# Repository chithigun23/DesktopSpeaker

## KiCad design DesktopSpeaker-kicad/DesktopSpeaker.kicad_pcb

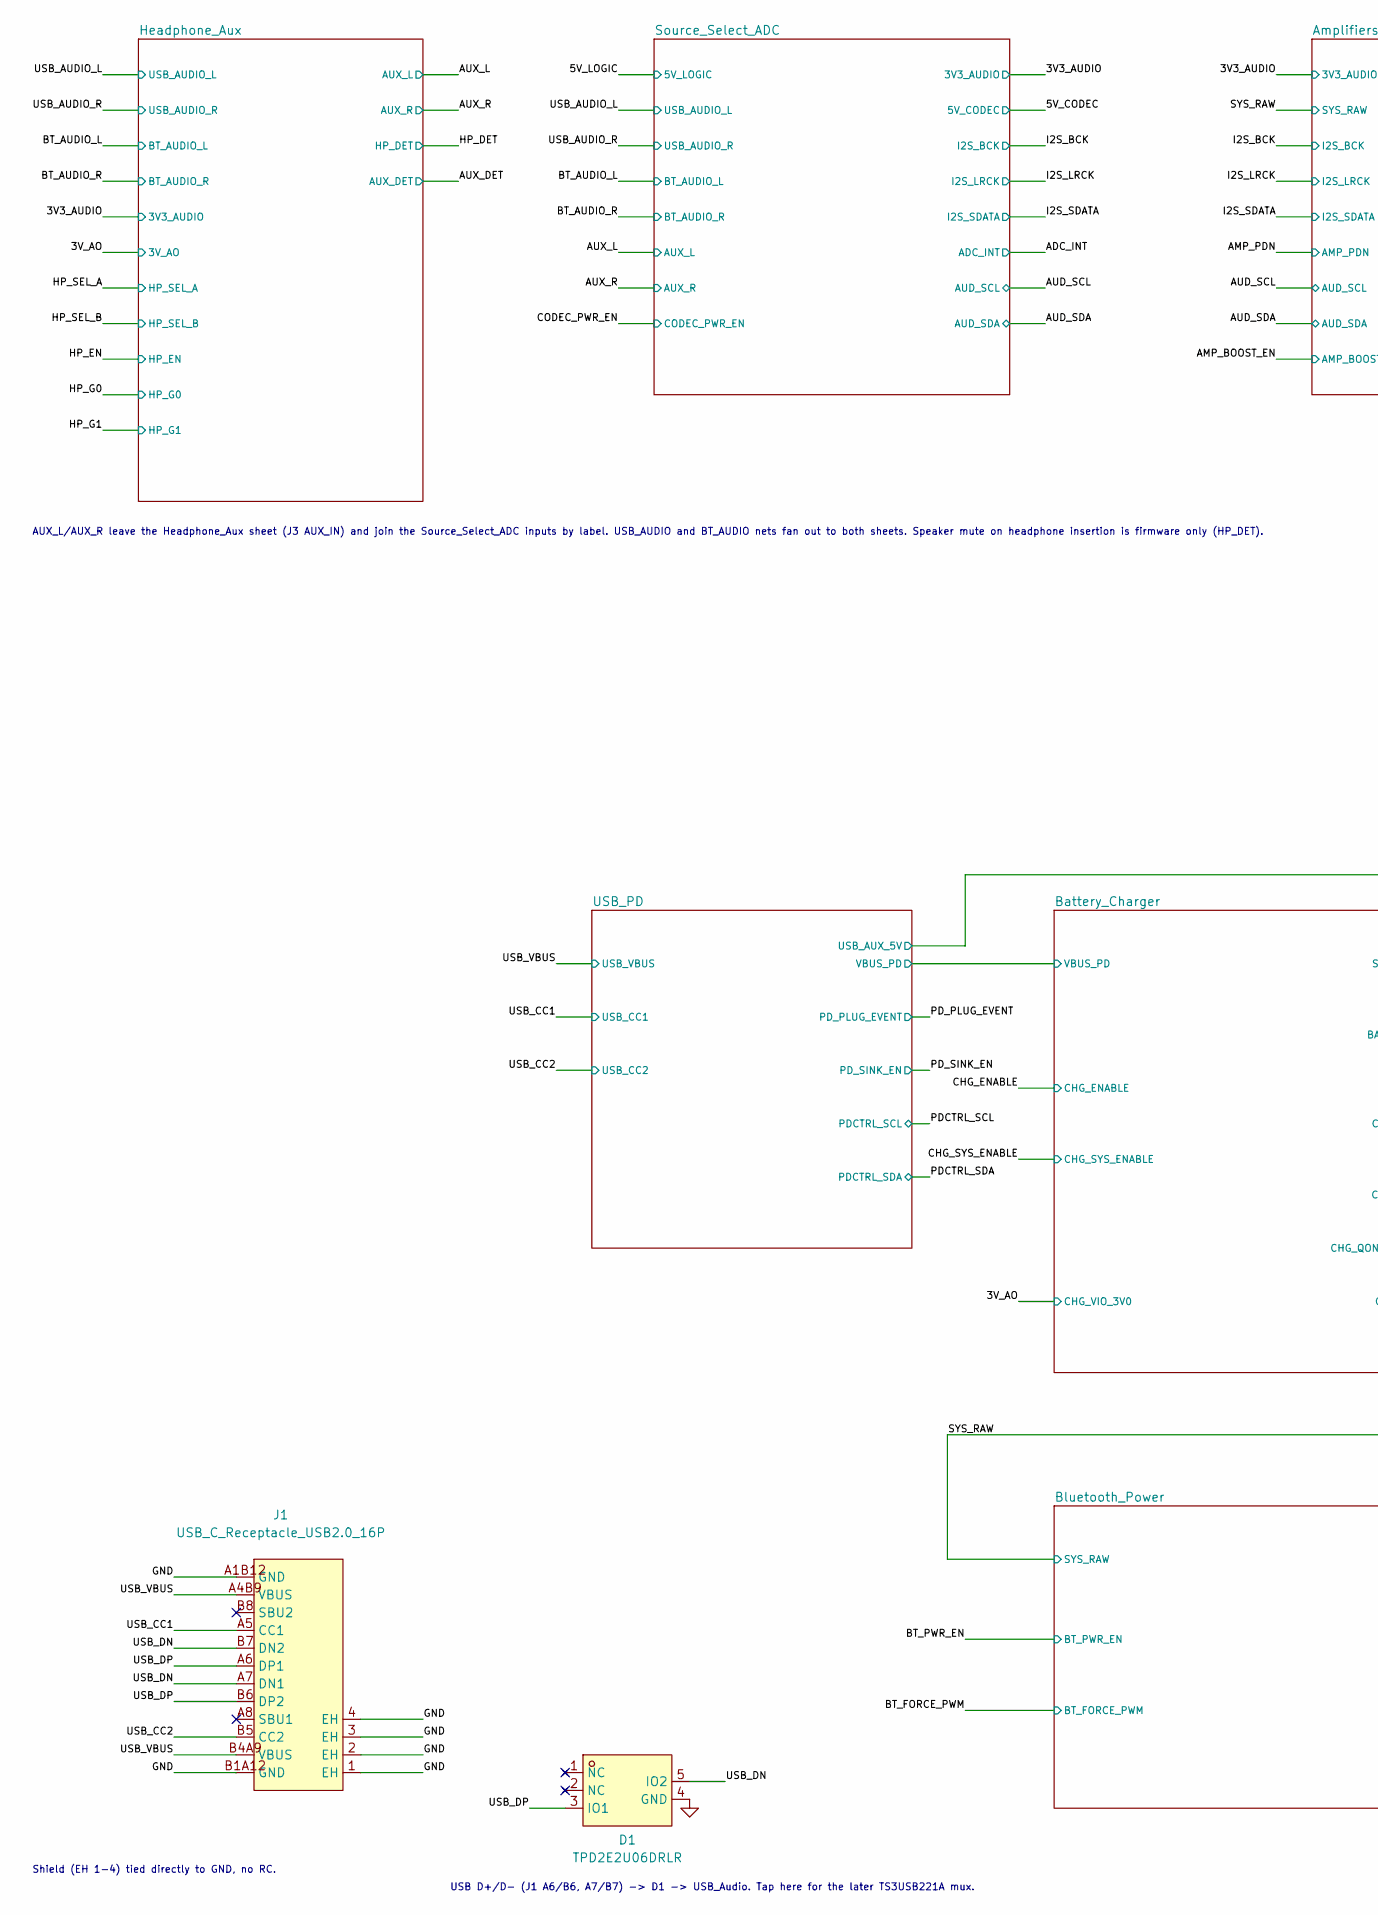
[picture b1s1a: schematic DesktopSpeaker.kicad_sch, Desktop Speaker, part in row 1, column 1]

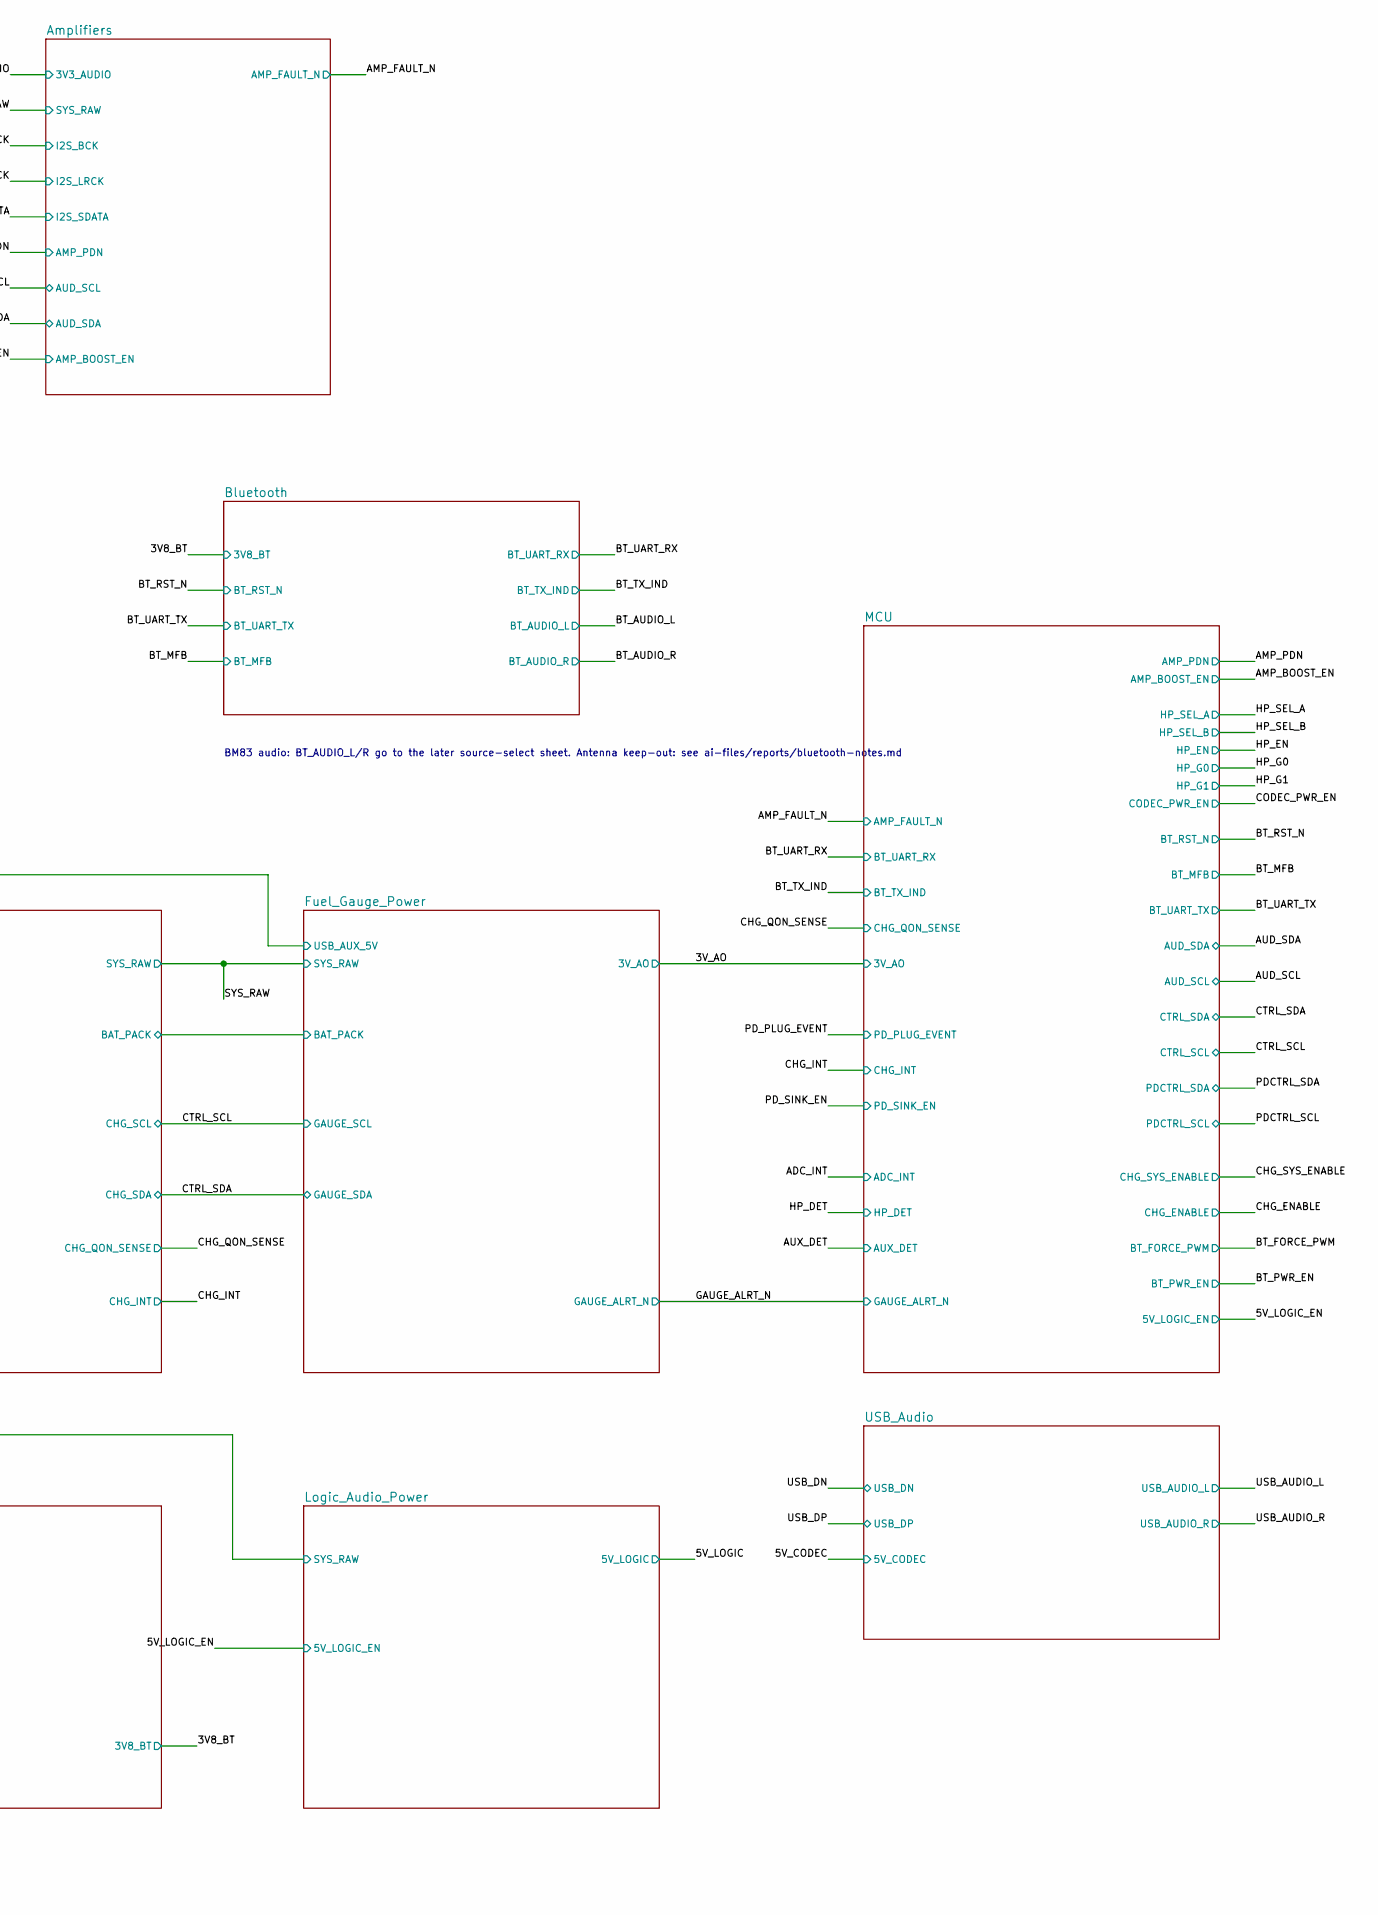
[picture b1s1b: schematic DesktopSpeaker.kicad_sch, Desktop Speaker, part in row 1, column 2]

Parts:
D1: TPD2E2U06DRLR; MPN TPD2E2U06DRLR; LCSC Part C1972959
J1: USB_C_Receptacle_USB2.0_16P; TYPE-C-31-M-12; MPN TYPE-C-31-M-12; LCSC Part C165948

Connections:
/USB_CC1: J1.A5 (CC1); also elsewhere on the board
/USB_CC2: J1.B5 (CC2); also elsewhere on the board
/USB_DN: D1.5 (IO2), J1.A7 (DN1), J1.B7 (DN2); also elsewhere on the board
/USB_DP: D1.3 (IO1), J1.A6 (DP1), J1.B6 (DP2); also elsewhere on the board
/USB_VBUS: J1.A4B9 (VBUS), J1.B4A9 (VBUS); also elsewhere on the board
GND: D1.4 (GND), J1.1 (EH), J1.2 (EH), J1.3 (EH), J1.4 (EH), J1.A1B12 (GND), J1.B1A12 (GND); also elsewhere on the board

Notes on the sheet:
USB D+/D- (J1 A6/B6, A7/B7) -> D1 -> USB_Audio. Tap here for the later TS3USB221A mux.
Shield (EH 1-4) tied directly to GND, no RC.
BM83 audio: BT_AUDIO_L/R go to the later source-select sheet. Antenna keep-out: see ai-files/reports/bluetooth-notes.md
AUX_L/AUX_R leave the Headphone_Aux sheet (J3 AUX_IN) and join the Source_Select_ADC inputs by label. USB_AUDIO and BT_AUDIO nets fan out to both sheets. Speaker mute on headphone insertion is firmware only (HP_DET).

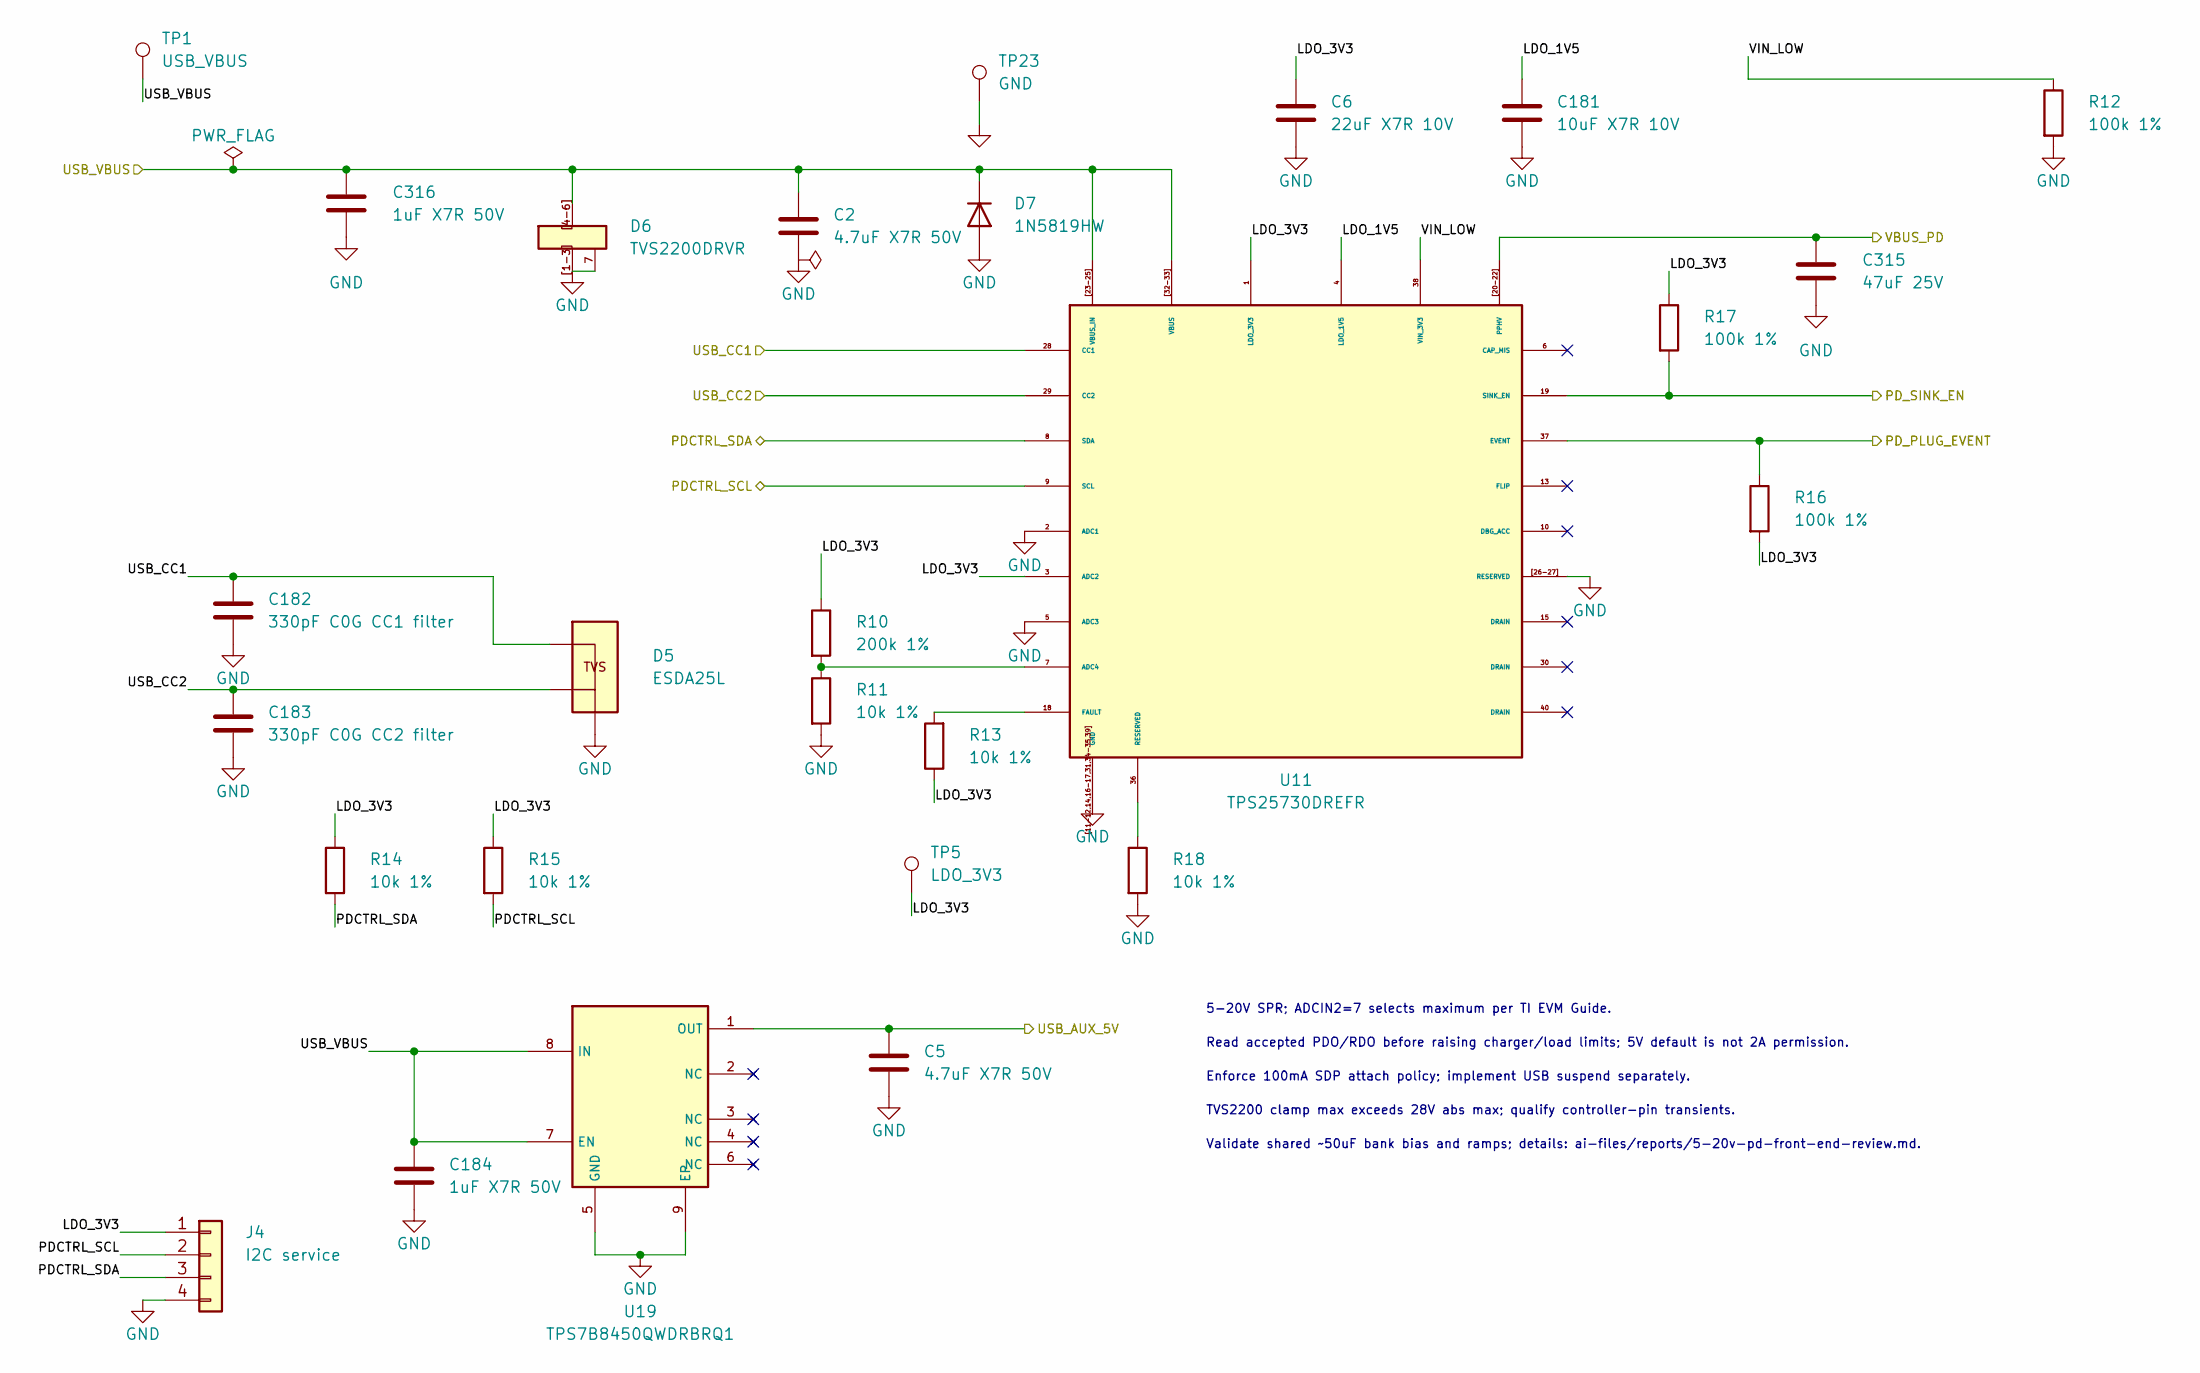
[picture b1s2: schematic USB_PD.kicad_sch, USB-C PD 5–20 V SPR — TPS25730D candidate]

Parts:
C2: 4.7uF X7R 50V; C_0805_2012Metric_Pad1.18x1.45mm_HandSolder; MPN C2012X7R1H475KT0A0E; LCSC Part C5159426
C5: 4.7uF X7R 50V; C_0805_2012Metric_Pad1.18x1.45mm_HandSolder; MPN C2012X7R1H475KT0A0E; LCSC C5159426
C6: 22uF X7R 10V; C_0805_2012Metric_Pad1.18x1.45mm_HandSolder; MPN GRM21BZ71A226ME15L; LCSC Part C907991
C181: 10uF X7R 10V; C_0805_2012Metric_Pad1.18x1.45mm_HandSolder; MPN CL21B106KPQNNNE; LCSC Part C32635
C182: 330pF C0G CC1 filter; C_0402_1005Metric_Pad0.74x0.62mm_HandSolder; MPN GRM1555C1H331JA01D; LCSC C76965
C183: 330pF C0G CC2 filter; C_0402_1005Metric_Pad0.74x0.62mm_HandSolder; MPN GRM1555C1H331JA01D; LCSC C76965
C184: 1uF X7R 50V; C_0805_2012Metric_Pad1.18x1.45mm_HandSolder; MPN CL21B105KBFNNNE; LCSC Part C28323
C315: 47uF 25V; PD_C_1206; MPN GRM31CR61E476ME44L; LCSC C403725
C316: 1uF X7R 50V; C_0805_2012Metric_Pad1.18x1.45mm_HandSolder; MPN CL21B105KBFNNNE; LCSC C28323
D5: ESDA25L; MPN ESDA25L; LCSC Part C95343
D6: TVS2200DRVR; MPN TVS2200DRVR; LCSC C523793
D7: 1N5819HW; PD_D_SOD123; MPN 1N5819HW-7-F; LCSC Part C82544
J4: I2C service; PD_SERVICE_HDR; MPN B-2100S04P-A110; LCSC C124378
R10: 200k 1%; R_0402_1005Metric_Pad0.72x0.64mm_HandSolder; MPN RC0402FR-07200KL; LCSC C114763
R11, R13, R14, R15, R18: 10k 1%; R_0402_1005Metric_Pad0.72x0.64mm_HandSolder; MPN RC0402FR-0710KL; LCSC Part C60490
R12, R16, R17: 100k 1%; R_0402_1005Metric_Pad0.72x0.64mm_HandSolder; MPN RC0402FR-07100KL; LCSC Part C60491
TP1: USB_VBUS; TestPoint_Keystone_5015_Micro_Mini
TP5: LDO_3V3; TestPoint_Keystone_5015_Micro_Mini
TP23: GND; TestPoint_Keystone_5010-5014_Multipurpose
U11: TPS25730DREFR; TPS25730D; MPN TPS25730DREFR; LCSC Part C22438973
U19: TPS7B8450QWDRBRQ1; TPS7B8450QWDRBRQ1_WSON-8; MPN TPS7B8450QWDRBRQ1; LCSC Part C3751394

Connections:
/Battery_Charger/VBUS_PD: C315.1, U11.20, U11.[20-22] (PPHV); also elsewhere on the board
/Fuel_Gauge_Power/USB_AUX_5V: C5.1, U19.1 (OUT); also elsewhere on the board
/PDCTRL_SCL: J4.2, R15.2, U11.9 (SCL); also elsewhere on the board
/PDCTRL_SDA: J4.3, R14.2, U11.8 (SDA); also elsewhere on the board
/PD_PLUG_EVENT: R16.1, U11.37 (EVENT); also elsewhere on the board
/PD_SINK_EN: R17.2, U11.19 (SINK_EN); also elsewhere on the board
/USB_CC1: C182.1, D5.1 (CC1/K1), U11.28 (CC1); also elsewhere on the board
/USB_CC2: C183.1, D5.2 (CC2/K2), U11.29 (CC2); also elsewhere on the board
/USB_PD/LDO_1V5: C181.1, U11.4 (LDO_1V5)
/USB_PD/LDO_3V3: C6.1, J4.1, R10.1, R13.1, R14.1, R15.1, R16.2, R17.1, TP5.1, U11.1 (LDO_3V3), U11.3 (ADC2)
/USB_PD/VIN_LOW: R12.1, U11.38 (VIN_3V3)
/USB_VBUS: C2.1, C184.1, C316.1, D6.4, D6.5, D6.6, D6.[4-6] (IN), D7.1 (K), TP1.1, U11.23, U11.32, U11.[23-25] (VBUS_IN), U11.[32-33] (VBUS), U19.7 (EN), U19.8 (IN); also elsewhere on the board
GND: C2.2, C5.2, C6.2, C181.2, C182.2, C183.2, C184.2, C315.2, C316.2, D5.3 (GND/A), D6.1, D6.2, D6.3, D6.7 (EP), D6.[1-3] (GND), D7.2 (A), J4.4, R11.2, R12.2, R18.2, TP23.1, U11.2 (ADC1), U11.5 (ADC3), U11.11, U11.12, U11.14, U11.16, U11.17, U11.26, U11.27, U11.31, U11.34, U11.39, U11.[11-12,14,16-17,31,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 (GND), U11.[26-27] (RESERVED), U19.5 (GND), U19.9 (EP); also elsewhere on the board
unnamed: R18.1, U11.36 (RESERVED)
unnamed: R10.2, R11.1, U11.7 (ADC4)
unnamed: R13.2, U11.18 (FAULT)

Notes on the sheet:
5-20V SPR; ADCIN2=7 selects maximum per TI EVM Guide.
Read accepted PDO/RDO before raising charger/load limits; 5V default is not 2A permission.
Enforce 100mA SDP attach policy; implement USB suspend separately.
TVS2200 clamp max exceeds 28V abs max; qualify controller-pin transients.
Validate shared ~50uF bank bias and ramps; details: ai-files/reports/5-20v-pd-front-end-review.md.

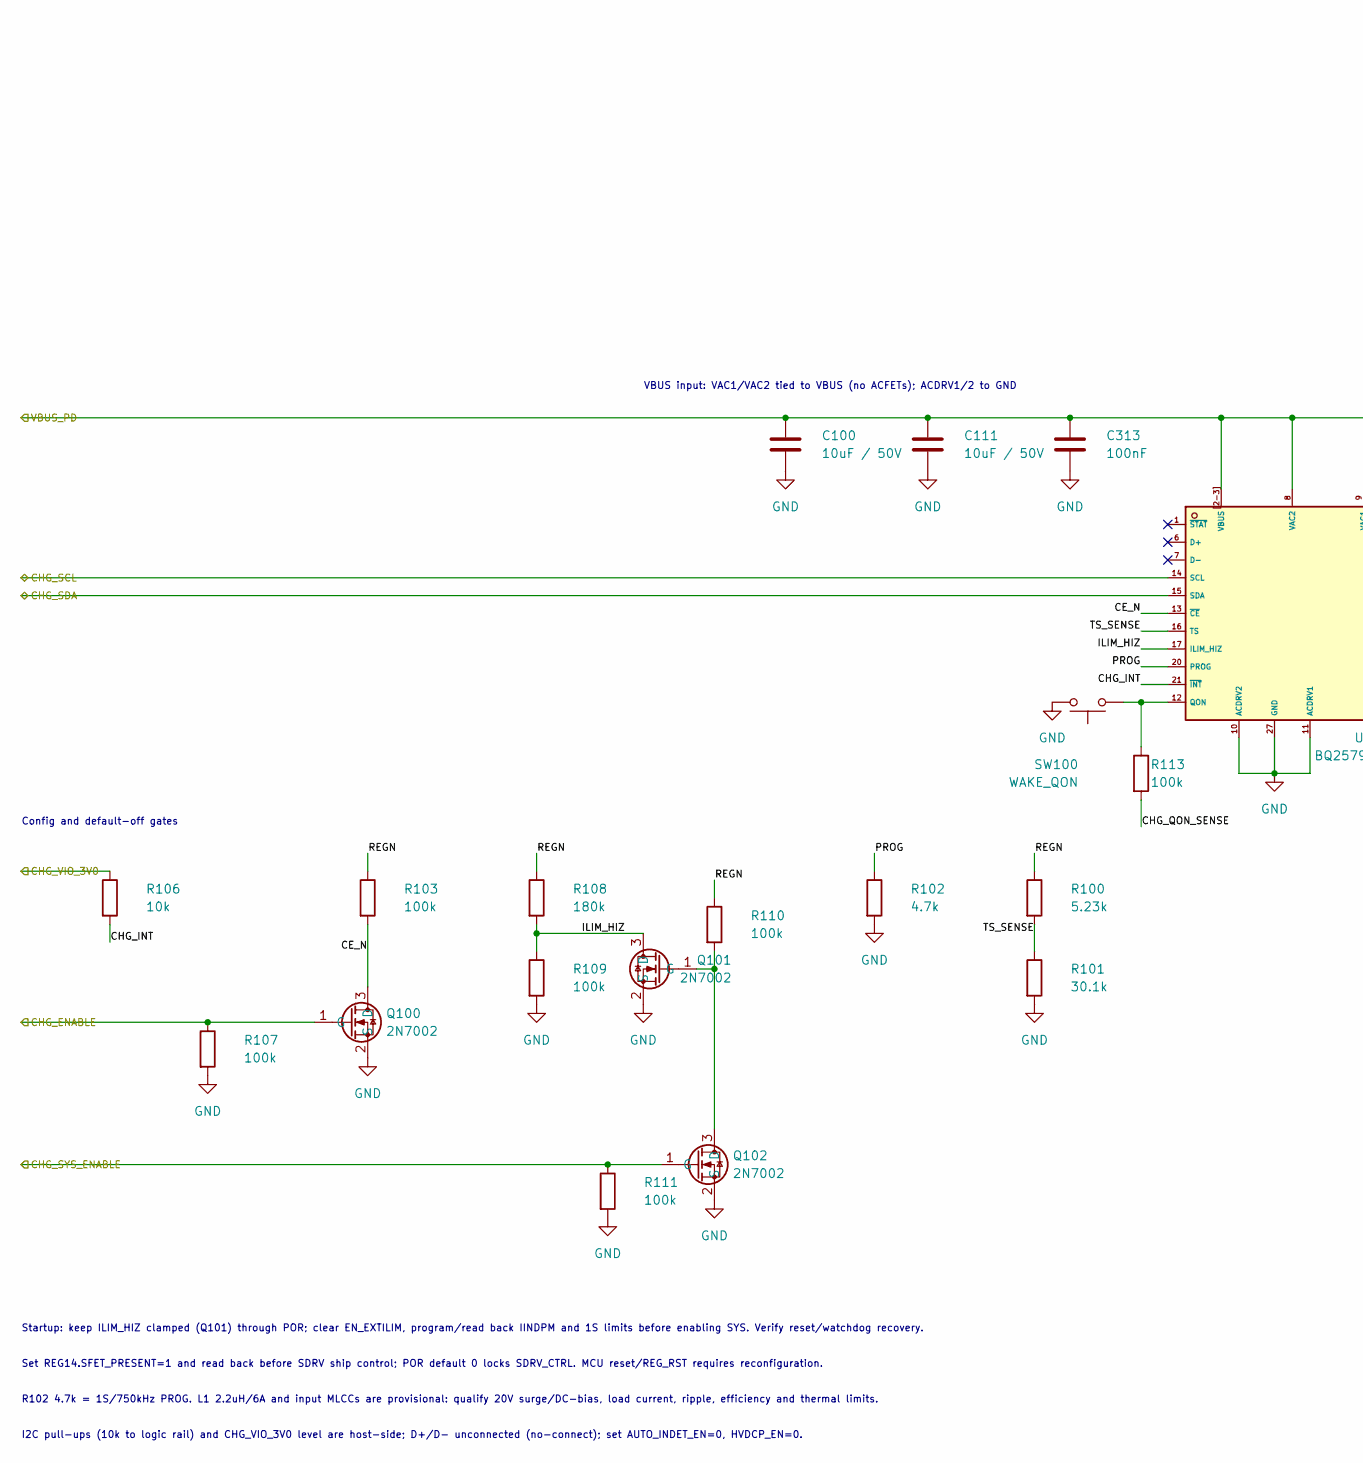
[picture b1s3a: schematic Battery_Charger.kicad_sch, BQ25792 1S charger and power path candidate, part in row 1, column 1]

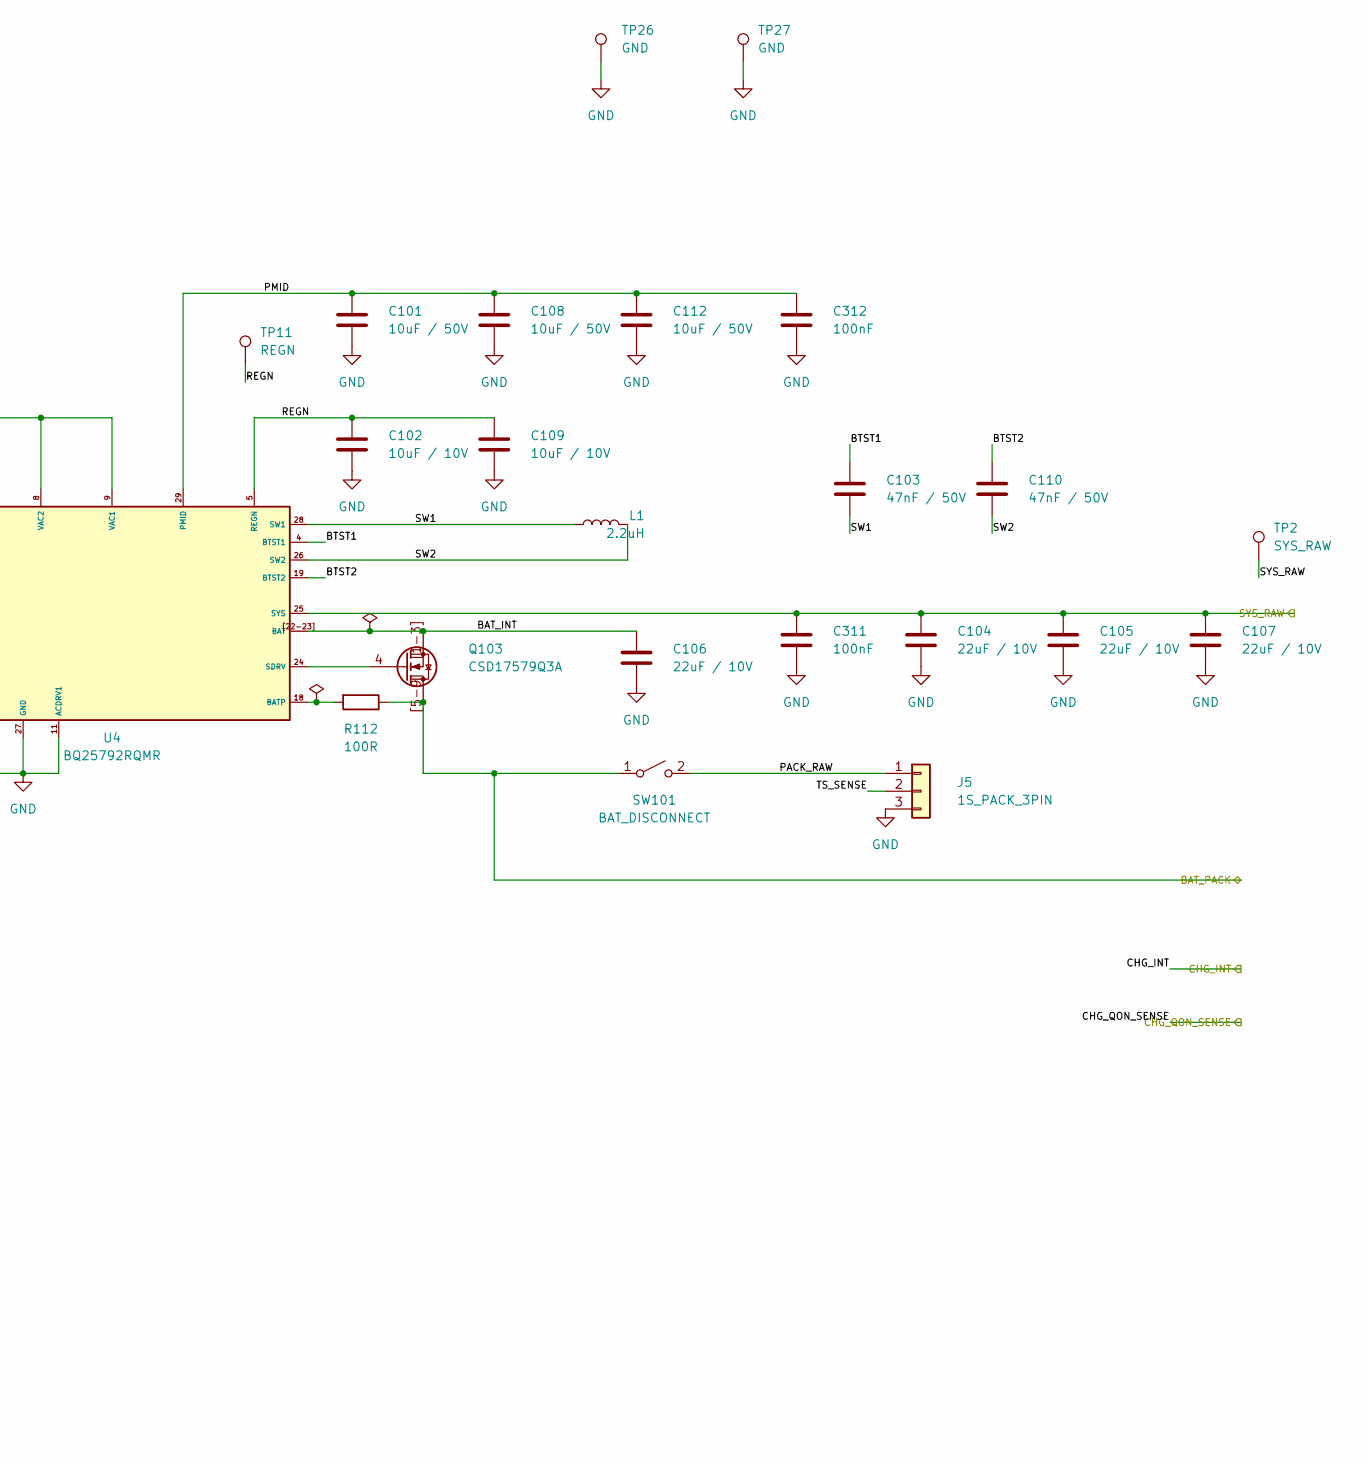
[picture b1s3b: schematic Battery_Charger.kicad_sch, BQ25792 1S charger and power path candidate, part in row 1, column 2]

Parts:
C100, C101, C108, C111, C112: 10uF / 50V; C_0805_2012Metric_Pad1.18x1.45mm_HandSolder; MPN GRM21BR61H106KE43L; LCSC C440198
C102, C109: 10uF / 10V; C_0805_2012Metric_Pad1.18x1.45mm_HandSolder; MPN CL21B106KPQNNNE; LCSC C32635
C103, C110: 47nF / 50V; C_0402_1005Metric_Pad0.74x0.62mm_HandSolder; MPN GRM155R71H473KE14D; LCSC C117757
C104, C105, C106, C107: 22uF / 10V; C_0805_2012Metric_Pad1.18x1.45mm_HandSolder; MPN GRM21BZ71A226ME15L; LCSC C907991
C311, C312, C313: 100nF; C_0402_1005Metric_Pad0.74x0.62mm_HandSolder; MPN GRM155R71H104KE14D; LCSC C77020
J5: 1S_PACK_3PIN; Molex_Micro-Fit_3.0_43650-0300_1x03_P3.00mm_Horizontal; MPN 43650-0300; LCSC C503478
L1: 2.2uH; Bourns_SRN6045TA-2R2Y; MPN SRN6045TA-2R2Y; LCSC Part C1332316
Q100: 2N7002; MPN 2N7002,215; LCSC C65189
Q101, Q102: 2N7002; MPN 2N7002,215; LCSC Part C65189
Q103: CSD17579Q3A; CSD17579Q3A_DNH0008A; MPN CSD17579Q3A; LCSC Part C97376
R100: 5.23k; R_0402_1005Metric_Pad0.72x0.64mm_HandSolder; MPN 0402WGF5231TCE; LCSC C25907
R101: 30.1k; R_0402_1005Metric_Pad0.72x0.64mm_HandSolder; MPN AC0402FR-0730K1L; LCSC C226982
R102: 4.7k; R_0402_1005Metric_Pad0.72x0.64mm_HandSolder; MPN RC0402FR-074K7L; LCSC C105871
R103, R107, R109, R110, R111, R113: 100k; R_0402_1005Metric_Pad0.72x0.64mm_HandSolder; MPN RC0402FR-07100KL; LCSC C60491
R106: 10k; R_0402_1005Metric_Pad0.72x0.64mm_HandSolder; MPN RC0402FR-0710KL; LCSC C60490
R108: 180k; R_0402_1005Metric_Pad0.72x0.64mm_HandSolder; MPN RC0402FR-07180KL; LCSC C138046
R112: 100R; R_0402_1005Metric_Pad0.72x0.64mm_HandSolder; MPN RC0402FR-07100RL; LCSC C106232
SW100: WAKE_QON; TE_1977066-1_Tact_RA_SMD; MPN 1977066-1; LCSC C2972219
SW101: BAT_DISCONNECT; SHOUHAN_KCD1-201-R_Rocker_D20_Panel; MPN GRB112B802BR1
TP2: SYS_RAW; TestPoint_Keystone_5015_Micro_Mini
TP11: REGN; TestPoint_Keystone_5015_Micro_Mini
TP26, TP27: GND; TestPoint_Keystone_5010-5014_Multipurpose
U4: BQ25792RQMR; MPN BQ25792RQMR; LCSC Part C2862876

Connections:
/3V_AO: R106.1; also elsewhere on the board
/Battery_Charger/BAT_INT: C106.1, Q103.1, Q103.2, Q103.3, Q103.[1-3] (S), U4.22, U4.23, U4.[22-23] (BAT)
/Battery_Charger/BTST1: C103.1, U4.4 (BTST1)
/Battery_Charger/BTST2: C110.1, U4.19 (BTST2)
/Battery_Charger/CE_N: Q100.3 (D), R103.2, U4.13 (~CE)
/Battery_Charger/ILIM_HIZ: Q101.3 (D), R108.2, R109.1, U4.17 (ILIM_HIZ)
/Battery_Charger/PACK_RAW: J5.1, SW101.2 (B)
/Battery_Charger/PMID: C101.1, C108.1, C112.1, C312.1, U4.29 (PMID)
/Battery_Charger/PROG: R102.1, U4.20 (PROG)
/Battery_Charger/REGN: C102.1, C109.1, R100.1, R103.1, R108.1, R110.1, TP11.1, U4.5 (REGN)
/Battery_Charger/SW1: C103.2, L1.1, U4.28 (SW1)
/Battery_Charger/SW2: C110.2, L1.2, U4.26 (SW2)
/Battery_Charger/TS_SENSE: J5.2, R100.2, R101.1, U4.16 (TS)
/Battery_Charger/VBUS_PD: C100.1, C111.1, C313.1, U4.2, U4.3, U4.8 (VAC2), U4.9 (VAC1), U4.[2-3] (VBUS); also elsewhere on the board
/CHG_ENABLE: Q100.1 (G), R107.1; also elsewhere on the board
/CHG_INT: R106.2, U4.21 (~INT); also elsewhere on the board
/CHG_QON_SENSE: R113.2; also elsewhere on the board
/CHG_SYS_ENABLE: Q102.1 (G), R111.1; also elsewhere on the board
/CTRL_SCL: U4.14 (SCL); also elsewhere on the board
/CTRL_SDA: U4.15 (SDA); also elsewhere on the board
/Fuel_Gauge_Power/BAT_PACK: Q103.5, Q103.6, Q103.7, Q103.8, Q103.9, Q103.[5-9] (D), R112.1, SW101.1 (A); also elsewhere on the board
/SYS_RAW: C104.1, C105.1, C107.1, C311.1, TP2.1, U4.25 (SYS); also elsewhere on the board
GND: C100.2, C101.2, C102.2, C104.2, C105.2, C106.2, C107.2, C108.2, C109.2, C111.2, C112.2, C311.2, C312.2, C313.2, J5.3, Q100.2 (S), Q101.2 (S), Q102.2 (S), R101.2, R102.2, R107.2, R109.2, R111.2, SW100.2, TP26.1, TP27.1, U4.10 (ACDRV2), U4.11 (ACDRV1), U4.27 (GND); also elsewhere on the board
unnamed: Q101.1 (G), Q102.3 (D), R110.2
unnamed: Q103.4 (G), U4.24 (SDRV)
unnamed: R112.2, U4.18 (BATP)
unnamed: R113.1, SW100.1, U4.12 (QON)

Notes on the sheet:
VBUS input: VAC1/VAC2 tied to VBUS (no ACFETs); ACDRV1/2 to GND
Config and default-off gates
Startup: keep ILIM_HIZ clamped (Q101) through POR; clear EN_EXTILIM, program/read back IINDPM and 1S limits before enabling SYS. Verify reset/watchdog recovery.
Set REG14.SFET_PRESENT=1 and read back before SDRV ship control; POR default 0 locks SDRV_CTRL. MCU reset/REG_RST requires reconfiguration.
R102 4.7k = 1S/750kHz PROG. L1 2.2uH/6A and input MLCCs are provisional: qualify 20V surge/DC-bias, load current, ripple, efficiency and thermal limits.
I2C pull-ups (10k to logic rail) and CHG_VIO_3V0 level are host-side; D+/D- unconnected (no-connect); set AUTO_INDET_EN=0, HVDCP_EN=0.

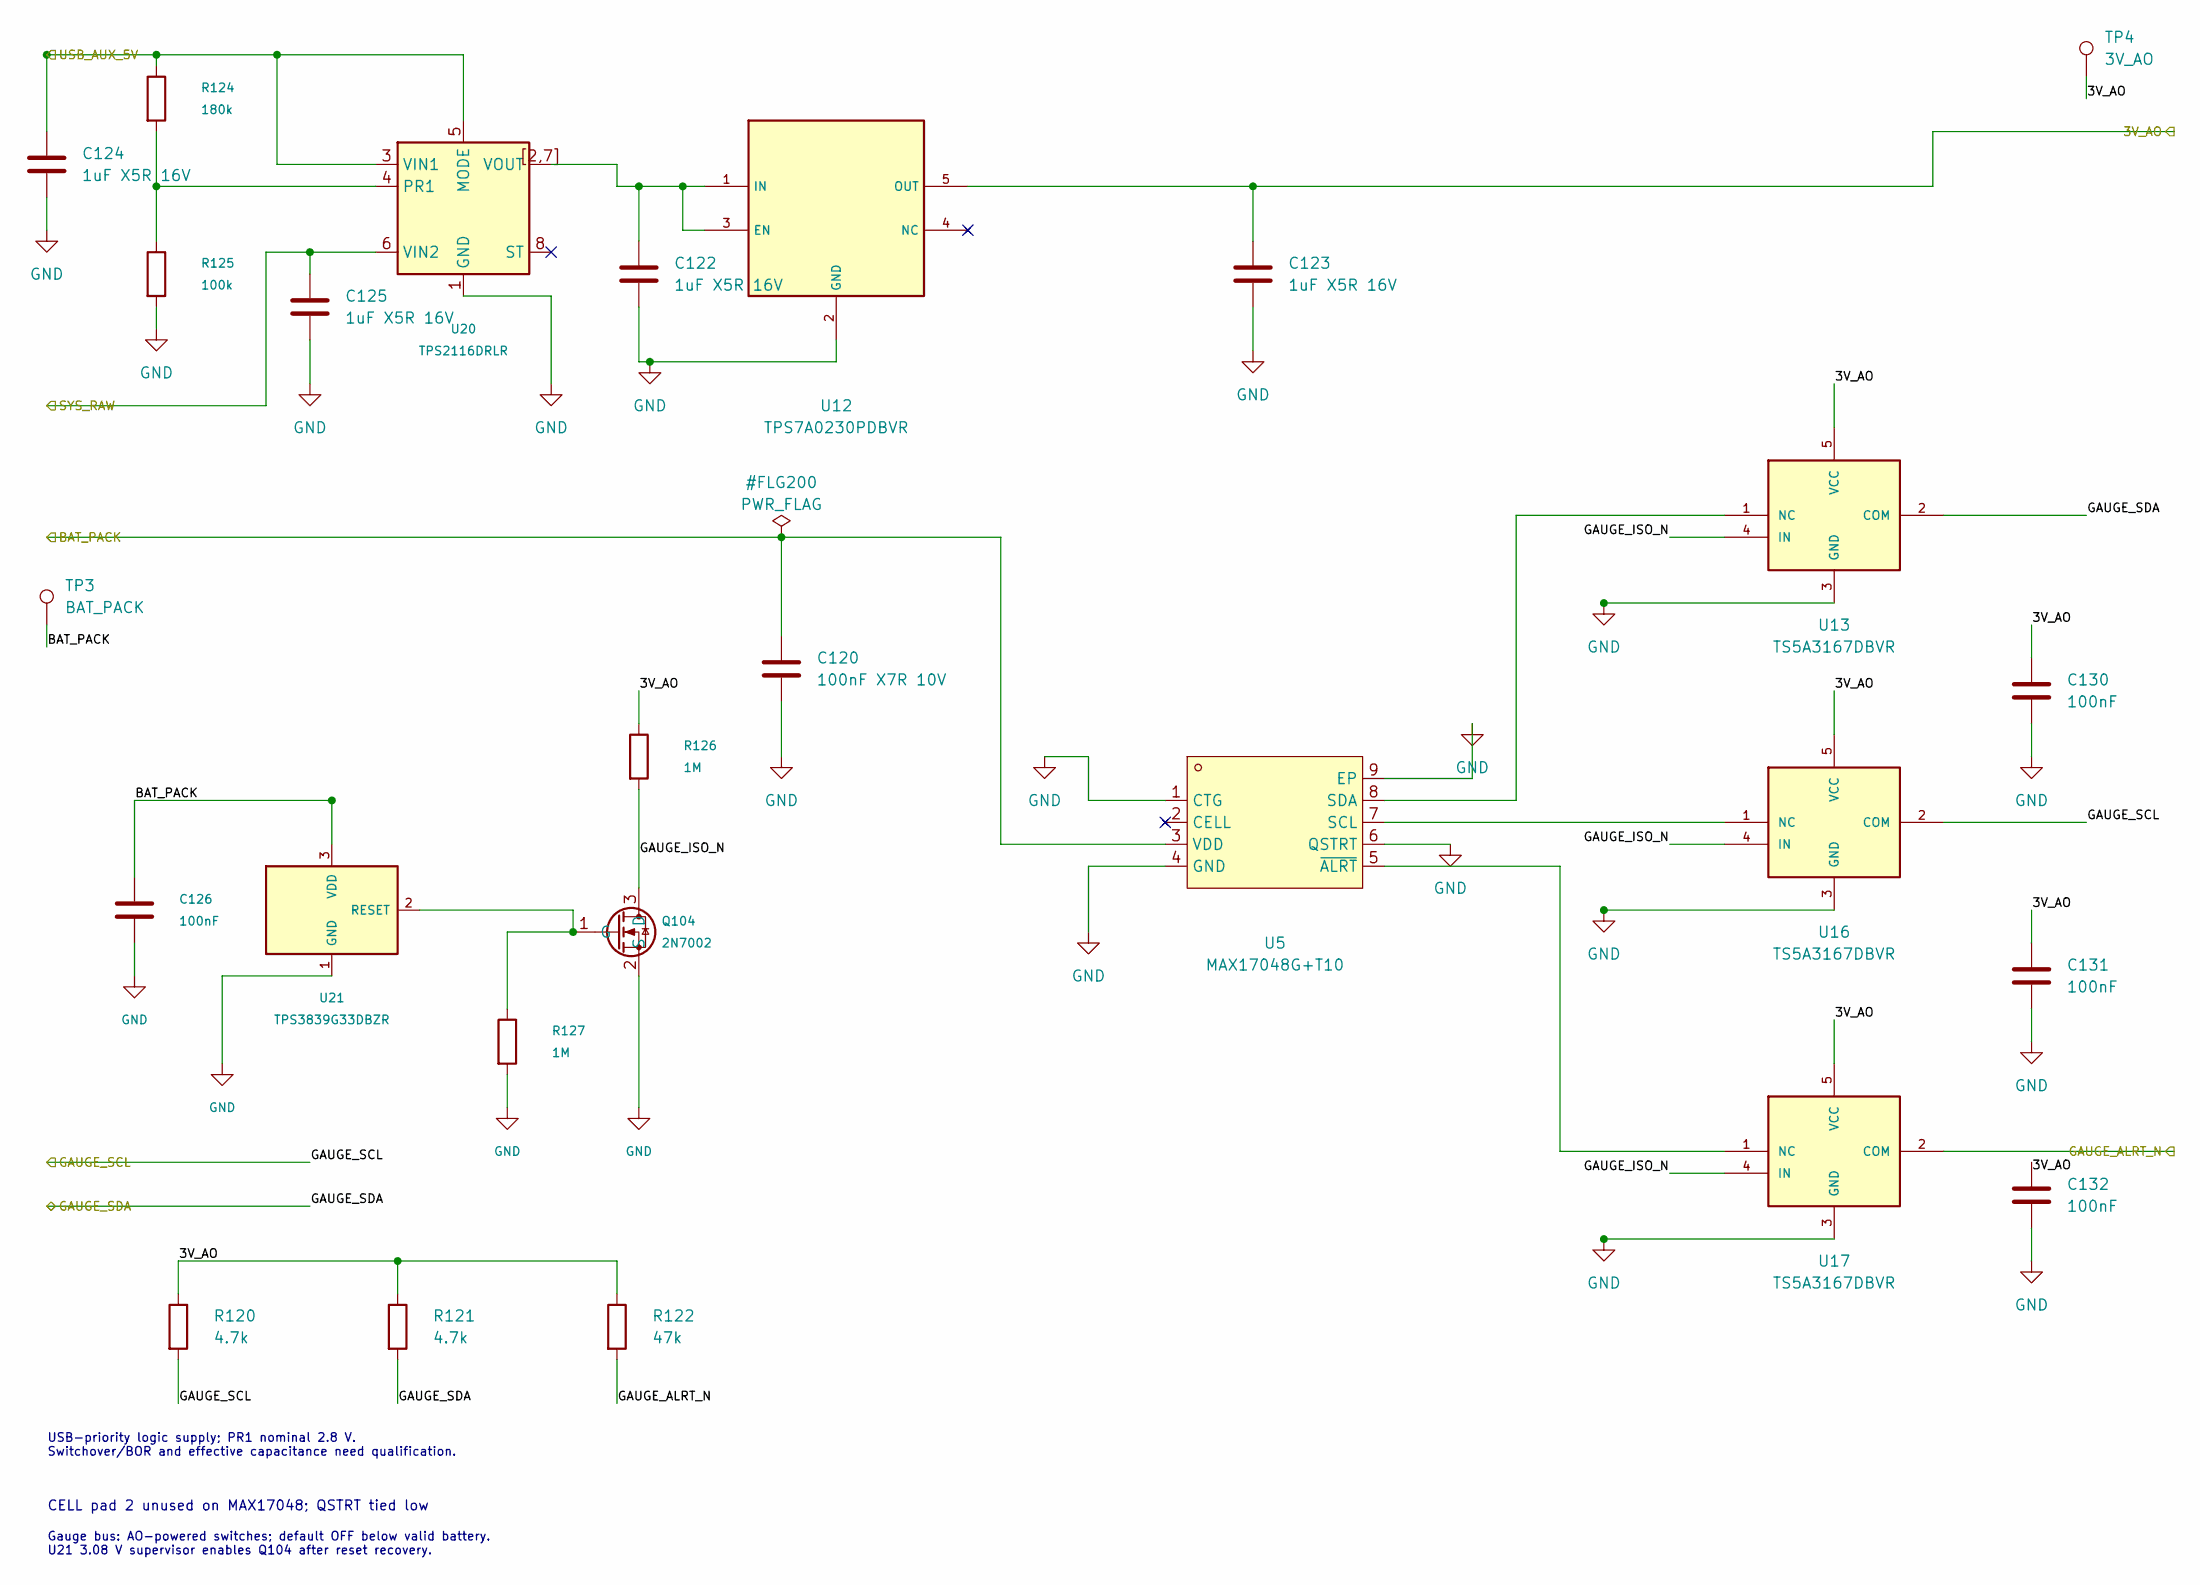
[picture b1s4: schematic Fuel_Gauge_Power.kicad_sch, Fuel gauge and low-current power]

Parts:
C120: 100nF X7R 10V; C_0402_1005Metric_Pad0.74x0.62mm_HandSolder; MPN GRM155R71H104KE14D; LCSC C77020
C122, C123, C124, C125: 1uF X5R 16V; C_0402_1005Metric_Pad0.74x0.62mm_HandSolder; MPN CL05A105KO5NNNC; LCSC C29266
C126, C130, C131, C132: 100nF; C_0402_1005Metric_Pad0.74x0.62mm_HandSolder; MPN GRM155R71H104KE14D; LCSC C77020
Q104: 2N7002; MPN 2N7002,215; LCSC C65189
R120, R121: 4.7k; R_0402_1005Metric_Pad0.72x0.64mm_HandSolder; MPN RC0402FR-074K7L
R122: 47k; R_0402_1005Metric_Pad0.72x0.64mm_HandSolder; MPN RC0402FR-0747KL
R124: 180k; R_0402_1005Metric_Pad0.72x0.64mm_HandSolder; MPN RC0402FR-07180KL
R125: 100k; R_0402_1005Metric_Pad0.72x0.64mm_HandSolder; MPN RC0402FR-07100KL; LCSC C60491
R126, R127: 1M; R_0402_1005Metric_Pad0.72x0.64mm_HandSolder; MPN RC0402FR-071ML
TP3: BAT_PACK; TestPoint_Keystone_5015_Micro_Mini
TP4: 3V_AO; TestPoint_Keystone_5015_Micro_Mini
U5: MAX17048G+T10; MPN MAX17048G+T10; LCSC Part C2682616
U12: TPS7A0230PDBVR; MPN TPS7A0230PDBVR; LCSC C3747031
U13, U16, U17: TS5A3167DBVR; MPN TS5A3167DBVR; LCSC C128416
U20: TPS2116DRLR; MPN TPS2116DRLR; LCSC C3235557
U21: TPS3839G33DBZR; MPN TPS3839G33DBZR; LCSC Part C485802

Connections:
/3V_AO: C123.1, C130.1, C131.1, C132.1, R120.1, R121.1, R122.1, R126.1, TP4.1, U12.5 (OUT), U13.5 (VCC), U16.5 (VCC), U17.5 (VCC); also elsewhere on the board
/CTRL_SCL: R120.2, U16.2 (COM); also elsewhere on the board
/CTRL_SDA: R121.2, U13.2 (COM); also elsewhere on the board
/Fuel_Gauge_Power/BAT_PACK: C120.1, C126.1, TP3.1, U5.3 (VDD), U21.3 (VDD); also elsewhere on the board
/Fuel_Gauge_Power/GAUGE_ISO_N: Q104.3 (D), R126.2, U13.4 (IN), U16.4 (IN), U17.4 (IN)
/Fuel_Gauge_Power/USB_AUX_5V: C124.1, R124.1, U20.3 (VIN1), U20.5 (MODE); also elsewhere on the board
/GAUGE_ALRT_N: R122.2, U17.2 (COM); also elsewhere on the board
/SYS_RAW: C125.1, U20.6 (VIN2); also elsewhere on the board
GND: C120.2, C122.2, C123.2, C124.2, C125.2, C126.2, C130.2, C131.2, C132.2, Q104.2 (S), R125.2, R127.2, U5.1 (CTG), U5.4 (GND), U5.6 (QSTRT), U5.9 (EP), U12.2 (GND), U13.3 (GND), U16.3 (GND), U17.3 (GND), U20.1 (GND), U21.1 (GND); also elsewhere on the board
unnamed: Q104.1 (G), R127.1, U21.2 (RESET)
unnamed: C122.1, U12.1 (IN), U12.3 (EN), U20.2, U20.7, U20.[2,7] (VOUT)
unnamed: U5.8 (SDA), U13.1 (NC)
unnamed: U5.7 (SCL), U16.1 (NC)
unnamed: U5.5 (~ALRT), U17.1 (NC)
unnamed: R124.2, R125.1, U20.4 (PR1)

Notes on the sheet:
CELL pad 2 unused on MAX17048; QSTRT tied low
Gauge bus: AO-powered switches; default OFF below valid battery. U21 3.08 V supervisor enables Q104 after reset recovery.
USB-priority logic supply; PR1 nominal 2.8 V. Switchover/BOR and effective capacitance need qualification.
